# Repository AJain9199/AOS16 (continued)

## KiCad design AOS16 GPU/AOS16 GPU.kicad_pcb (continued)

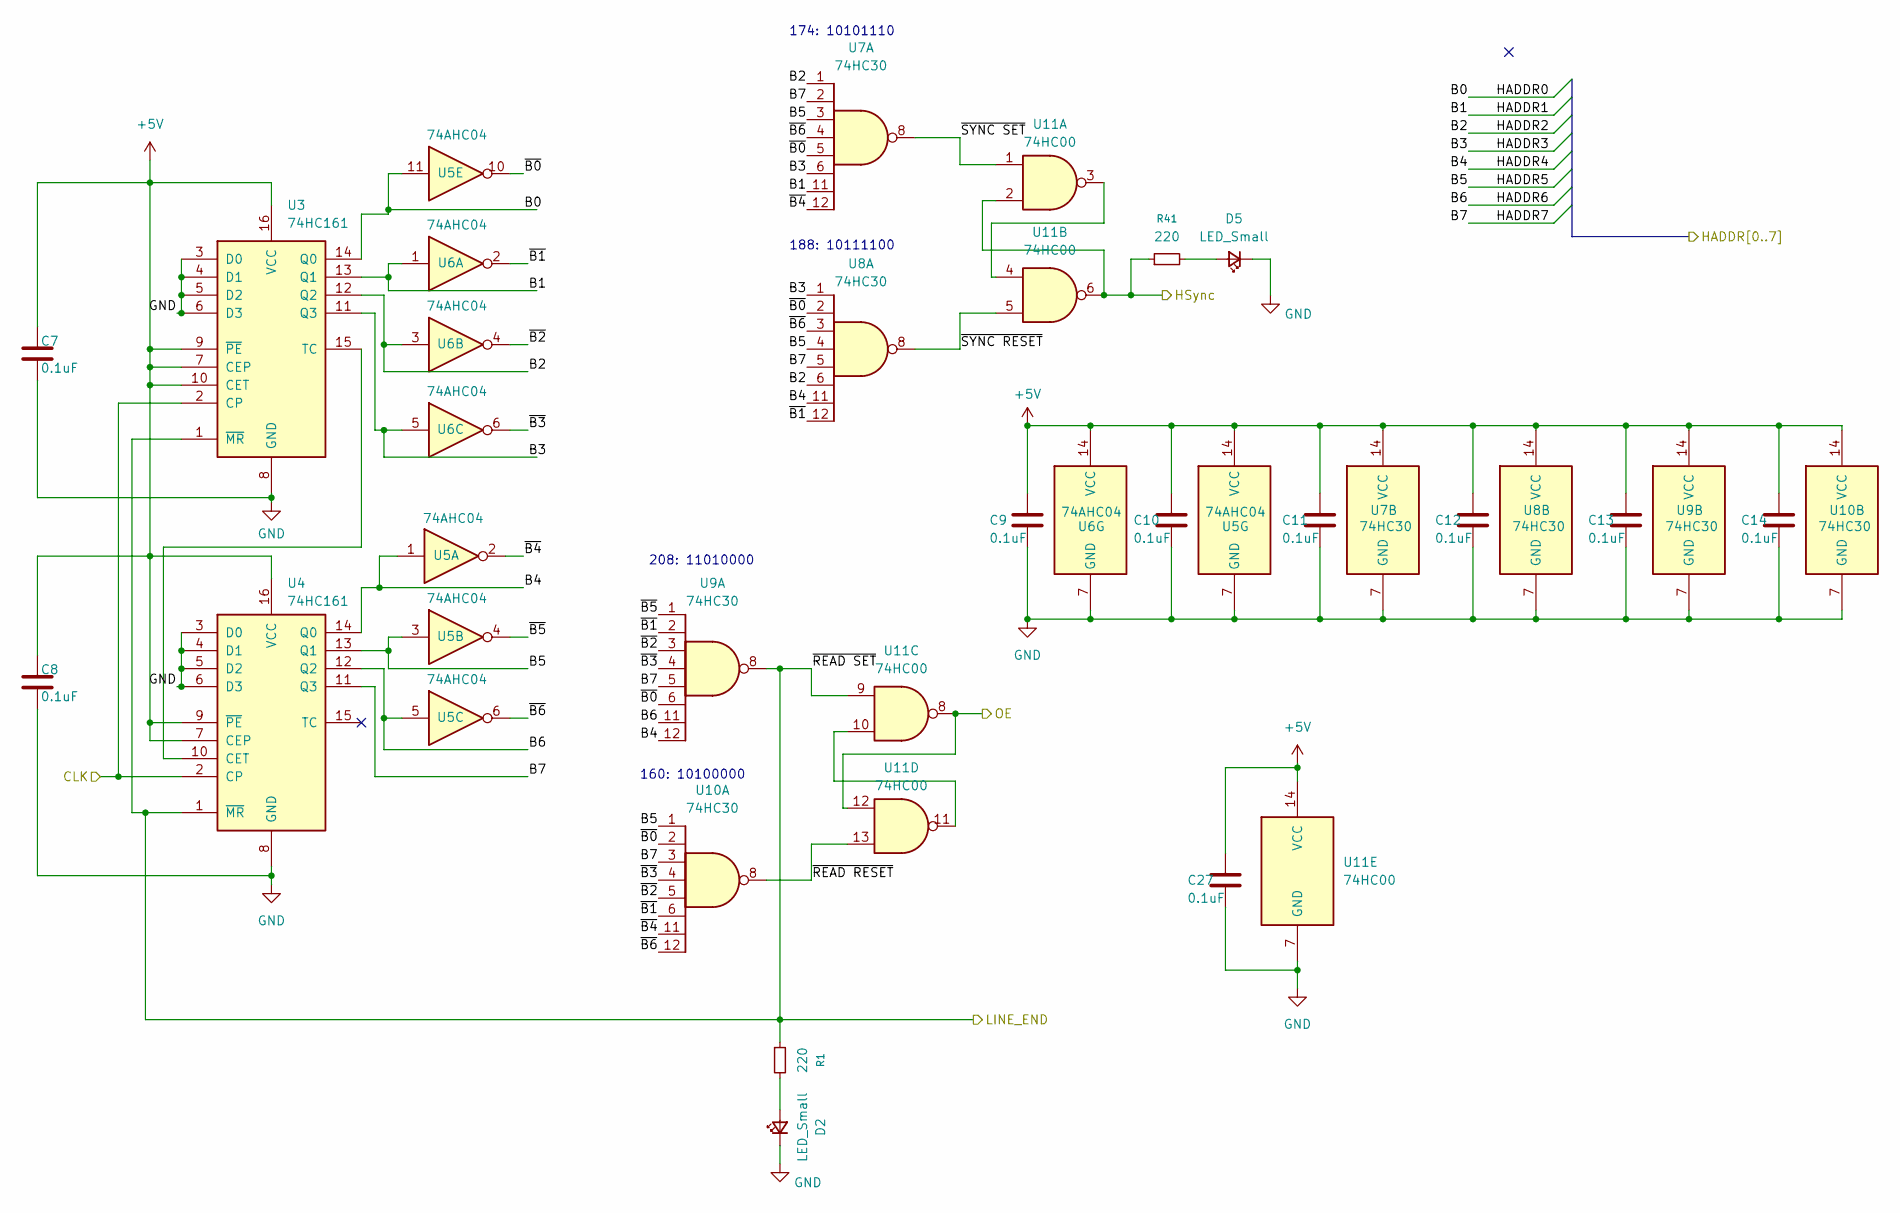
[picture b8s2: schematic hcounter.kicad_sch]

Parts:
C7, C8, C9, C10, C11, C12, C13, C14, C27: 0.1uF; C_0603_1608Metric
D2, D5: LED_Small; LED_0603_1608Metric
R1, R41: 220; R_0603_1608Metric
U3, U4: 74HC161; SOIC-16_3.9x9.9mm_P1.27mm
U5, U6: 74AHC04; SOIC-14_3.9x8.7mm_P1.27mm
U7, U8, U9, U10: 74HC30; SOIC-14_3.9x8.7mm_P1.27mm
U11: 74HC00; SOIC-14_3.9x8.7mm_P1.27mm

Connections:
+5V: C7.1, C8.1, C9.1, C10.1, C11.1, C12.1, C13.1, C14.1, C27.1, U3.7 (CEP), U3.9 (~PE), U3.10 (CET), U3.16 (VCC), U4.7 (CEP), U4.9 (~PE), U4.16 (VCC), U5.14 (VCC), U6.14 (VCC), U7.14 (VCC), U8.14 (VCC), U9.14 (VCC), U10.14 (VCC), U11.14 (VCC); also elsewhere on the board
/9mhz: U3.2 (CP), U4.2 (CP); also elsewhere on the board
/HCounter/OE: U11.8, U11.12; also elsewhere on the board
/HCounter/~B0: U5.10, U7.5, U8.2, U9.6, U10.2
/HCounter/~B1: U6.2, U8.12, U9.2, U10.6
/HCounter/~B2: U6.4, U9.3, U10.5
/HCounter/~B3: U6.6, U9.4, U10.4
/HCounter/~B4: U5.2, U7.12, U10.11
/HCounter/~B5: U5.4, U9.1
/HCounter/~B6: U5.6, U7.4, U8.3, U10.12
/HCounter/~READ RESET: U10.8, U11.13
/HCounter/~READ SET: R1.1, U3.1 (~MR), U4.1 (~MR), U9.8, U11.9; also elsewhere on the board
/HCounter/~SYNC RESET: U8.8, U11.5
/HCounter/~SYNC SET: U7.8, U11.1
/RAM_ADDR0: U3.14 (Q0), U5.11; also elsewhere on the board
/RAM_ADDR1: U3.13 (Q1), U6.1, U7.11; also elsewhere on the board
/RAM_ADDR2: U3.12 (Q2), U6.3, U7.1, U8.6; also elsewhere on the board
/RAM_ADDR3: U3.11 (Q3), U6.5, U7.6, U8.1; also elsewhere on the board
/RAM_ADDR4: U4.14 (Q0), U5.1, U8.11, U9.12; also elsewhere on the board
/RAM_ADDR5: U4.13 (Q1), U5.3, U7.3, U8.4, U10.1; also elsewhere on the board
/RAM_ADDR6: U4.12 (Q2), U5.5, U9.11; also elsewhere on the board
/RAM_ADDR7: U4.11 (Q3), U7.2, U8.5, U9.5, U10.3; also elsewhere on the board
/h_sync: R41.1, U11.2, U11.6; also elsewhere on the board
GND: C7.2, C8.2, C9.2, C10.2, C11.2, C12.2, C13.2, C14.2, C27.2, D2.1 (K), D5.1 (K), U3.3 (D0), U3.4 (D1), U3.5 (D2), U3.6 (D3), U3.8 (GND), U4.3 (D0), U4.4 (D1), U4.5 (D2), U4.6 (D3), U4.8 (GND), U5.7 (GND), U6.7 (GND), U7.7 (GND), U8.7 (GND), U9.7 (GND), U10.7 (GND), U11.7 (GND); also elsewhere on the board
unnamed: D2.2 (A), R1.2
unnamed: D5.2 (A), R41.2
unnamed: U3.15 (TC), U4.10 (CET)
unnamed: U11.3, U11.4
unnamed: U11.10, U11.11

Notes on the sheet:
160: 10100000
188: 10111100
174: 10101110
208: 11010000

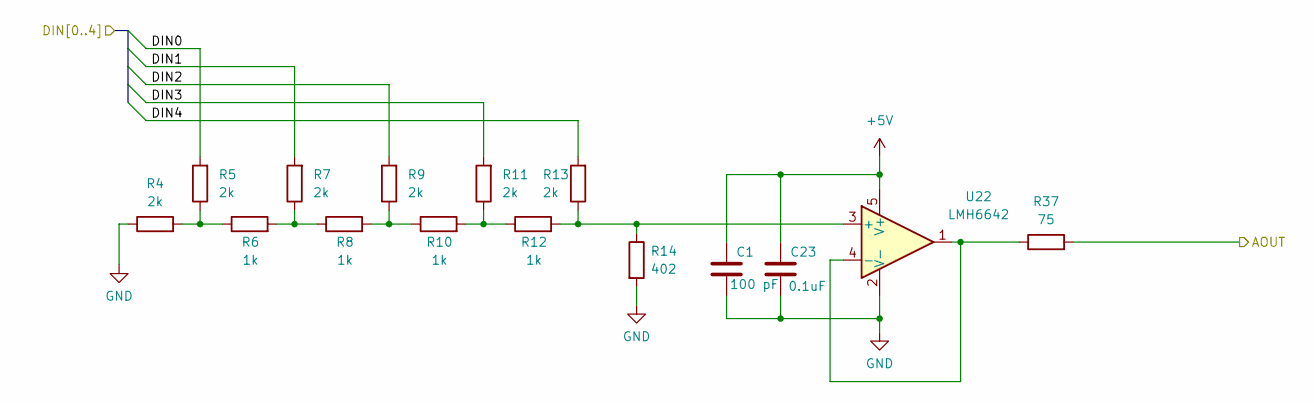
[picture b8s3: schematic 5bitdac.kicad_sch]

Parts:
C1: 100 pF; C_0603_1608Metric
C23: 0.1uF; C_0603_1608Metric
R4, R5, R7, R9, R11, R13: 2k; R_0603_1608Metric
R6, R8, R10, R12: 1k; R_0603_1608Metric
R14: 402; R_0402_1005Metric
R37: 75; R_0603_1608Metric
U22: LMH6642; SOT-23-5

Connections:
+5V: C1.1, C23.1, U22.5 (V+); also elsewhere on the board
/5-bit DAC1/AOUT: R37.2; also elsewhere on the board
/MEMIN5: R5.2; also elsewhere on the board
/MEMIN6: R7.2; also elsewhere on the board
/MEMIN7: R9.2; also elsewhere on the board
/MEMIN8: R11.2; also elsewhere on the board
/MEMIN9: R13.2; also elsewhere on the board
GND: C1.2, C23.2, R4.1, R14.2, U22.2 (V-); also elsewhere on the board
unnamed: R4.2, R5.1, R6.1
unnamed: R6.2, R7.1, R8.1
unnamed: R8.2, R9.1, R10.1
unnamed: R10.2, R11.1, R12.1
unnamed: R12.2, R13.1, R14.1, U22.3 (+)
unnamed: R37.1, U22.1, U22.4 (-)

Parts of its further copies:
C2, C4: 100 pF; C_0603_1608Metric
C24, C25: 0.1uF; C_0603_1608Metric
R15, R16, R18, R20, R22, R24, R26, R27, R29, R31, R33, R35: 2k; R_0603_1608Metric
R17, R19, R21, R23, R28, R30, R32, R34: 1k; R_0603_1608Metric
R25, R36: 402; R_0402_1005Metric
R38, R39: 75; R_0603_1608Metric
U23, U24: LMH6642; SOT-23-5

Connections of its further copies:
+5V: C2.1, C4.1, C24.1, C25.1, U23.5 (V+), U24.5 (V+); also elsewhere on the board
/5-bit DAC2/AOUT: R39.2; also elsewhere on the board
/5-bit DAC/AOUT: R38.2; also elsewhere on the board
/MEMIN0: R16.2; also elsewhere on the board
/MEMIN1: R18.2; also elsewhere on the board
/MEMIN2: R20.2; also elsewhere on the board
/MEMIN3: R22.2; also elsewhere on the board
/MEMIN4: R24.2; also elsewhere on the board
/MEMIN10: R27.2; also elsewhere on the board
/MEMIN11: R29.2; also elsewhere on the board
/MEMIN12: R31.2; also elsewhere on the board
/MEMIN13: R33.2; also elsewhere on the board
/MEMIN14: R35.2; also elsewhere on the board
GND: C2.2, C4.2, C24.2, C25.2, R15.1, R25.2, R26.1, R36.2, U23.2 (V-), U24.2 (V-); also elsewhere on the board
unnamed: R15.2, R16.1, R17.1
unnamed: R17.2, R18.1, R19.1
unnamed: R19.2, R20.1, R21.1
unnamed: R21.2, R22.1, R23.1
unnamed: R26.2, R27.1, R28.1
unnamed: R28.2, R29.1, R30.1
unnamed: R30.2, R31.1, R32.1
unnamed: R32.2, R33.1, R34.1
unnamed: R23.2, R24.1, R25.1, U23.3 (+)
unnamed: R38.1, U23.1, U23.4 (-)
unnamed: R34.2, R35.1, R36.1, U24.3 (+)
unnamed: R39.1, U24.1, U24.4 (-)

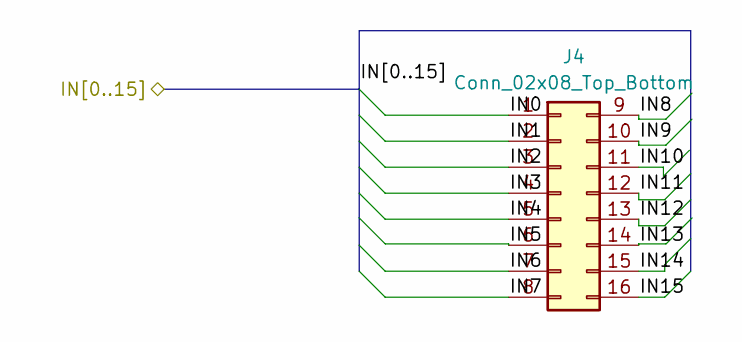
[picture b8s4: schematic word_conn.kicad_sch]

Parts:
J4: Conn_02x08_Top_Bottom; PinHeader_2x08_P2.54mm_Vertical

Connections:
/RAM_ADDR0: J4.1; also elsewhere on the board
/RAM_ADDR1: J4.2; also elsewhere on the board
/RAM_ADDR2: J4.3; also elsewhere on the board
/RAM_ADDR3: J4.4; also elsewhere on the board
/RAM_ADDR4: J4.5; also elsewhere on the board
/RAM_ADDR5: J4.6; also elsewhere on the board
/RAM_ADDR6: J4.7; also elsewhere on the board
/RAM_ADDR7: J4.8; also elsewhere on the board
/RAM_ADDR8: J4.9; also elsewhere on the board
/RAM_ADDR9: J4.10; also elsewhere on the board
/RAM_ADDR10: J4.11; also elsewhere on the board
/RAM_ADDR11: J4.12; also elsewhere on the board
/RAM_ADDR12: J4.13; also elsewhere on the board
/RAM_ADDR13: J4.14; also elsewhere on the board
/RAM_ADDR14: J4.15; also elsewhere on the board
/word_conn/IN15: J4.16

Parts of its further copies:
J5: Conn_02x08_Top_Bottom; PinHeader_2x08_P2.54mm_Vertical

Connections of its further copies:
/MEMIN0: J5.1; also elsewhere on the board
/MEMIN1: J5.2; also elsewhere on the board
/MEMIN2: J5.3; also elsewhere on the board
/MEMIN3: J5.4; also elsewhere on the board
/MEMIN4: J5.5; also elsewhere on the board
/MEMIN5: J5.6; also elsewhere on the board
/MEMIN6: J5.7; also elsewhere on the board
/MEMIN7: J5.8; also elsewhere on the board
/MEMIN8: J5.9; also elsewhere on the board
/MEMIN9: J5.10; also elsewhere on the board
/MEMIN10: J5.11; also elsewhere on the board
/MEMIN11: J5.12; also elsewhere on the board
/MEMIN12: J5.13; also elsewhere on the board
/MEMIN13: J5.14; also elsewhere on the board
/MEMIN14: J5.15; also elsewhere on the board
/MEMIN15: J5.16

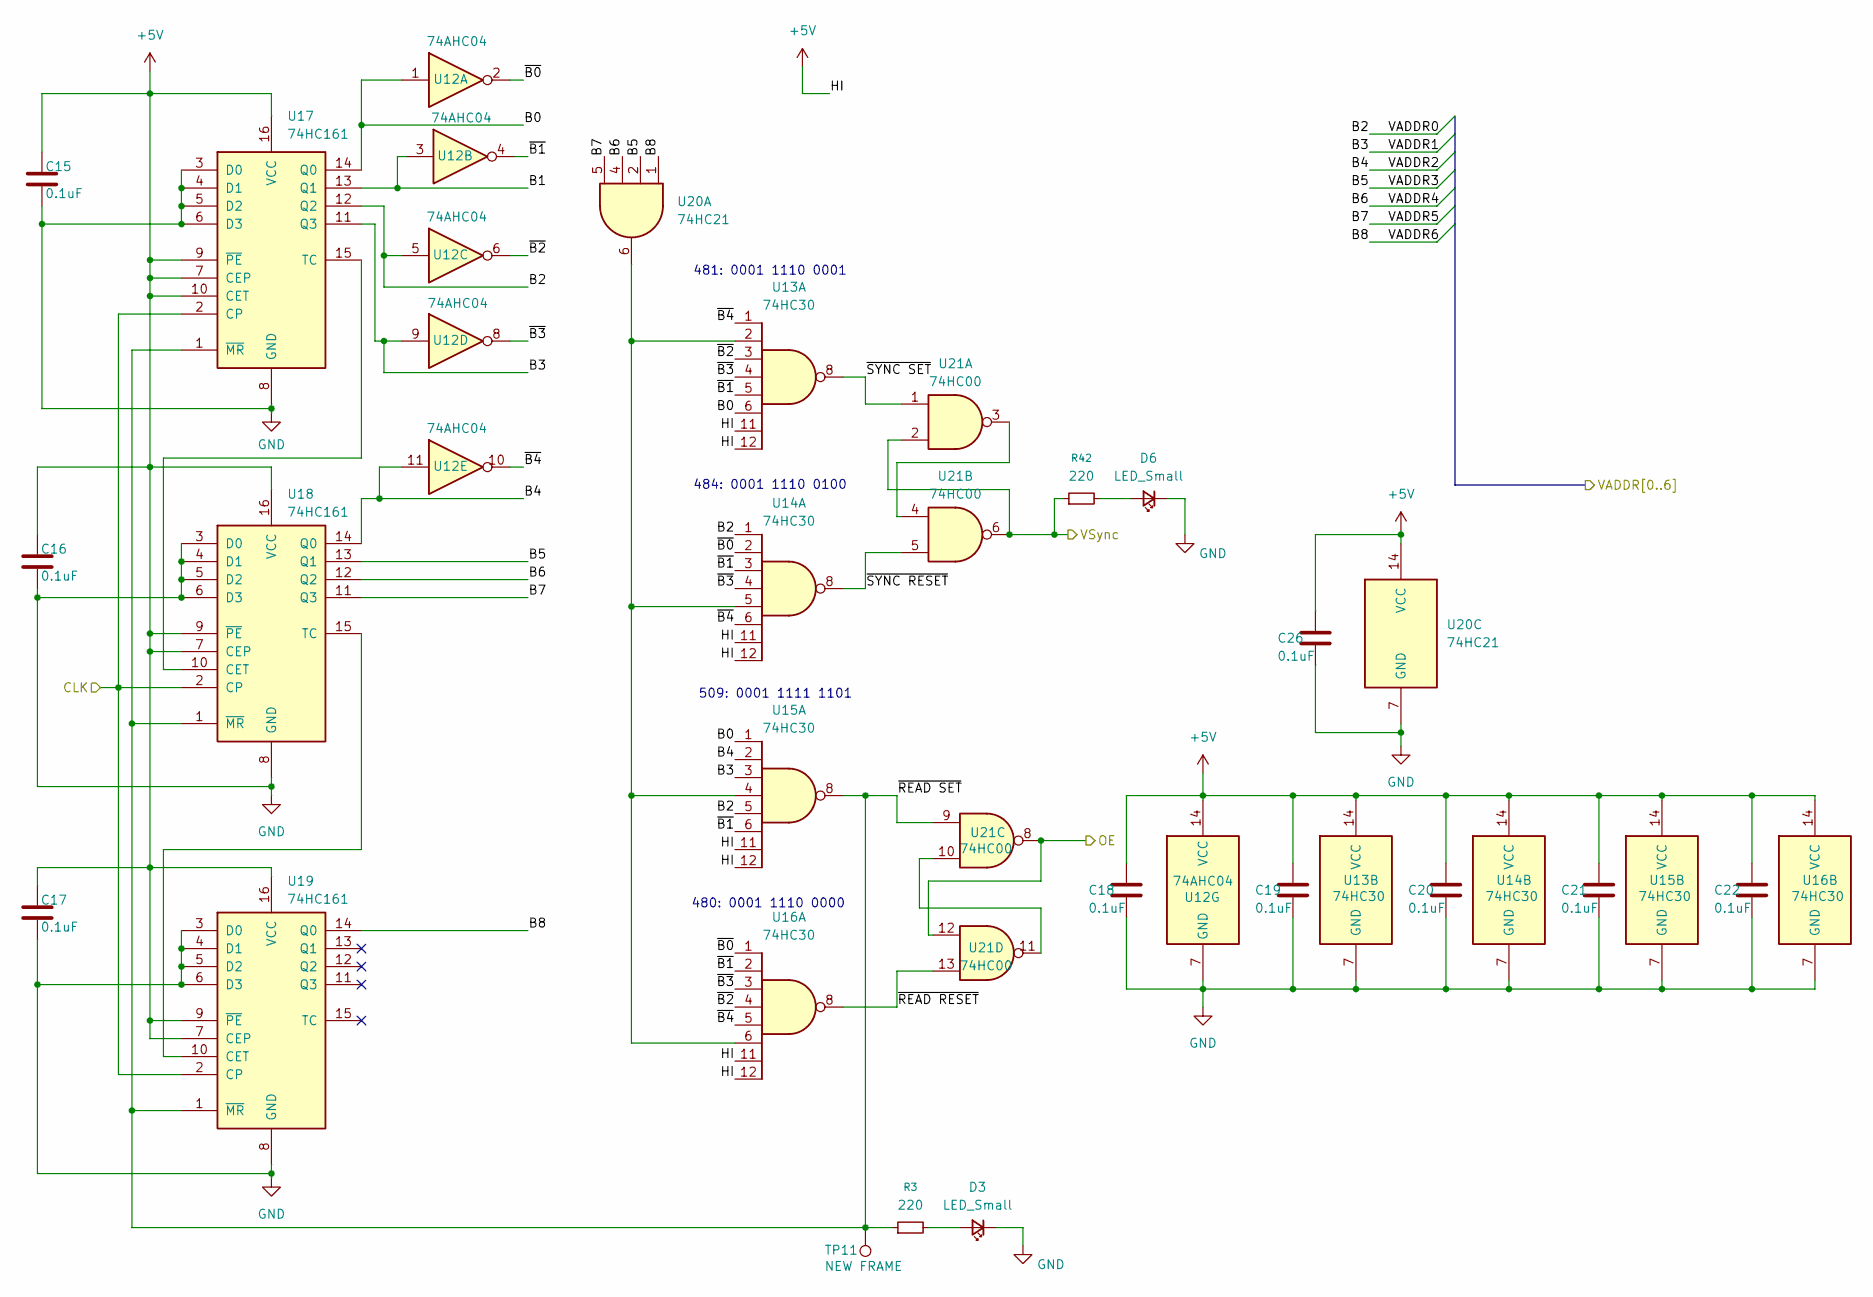
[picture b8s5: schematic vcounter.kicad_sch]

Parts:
C15, C16, C17, C18, C19, C20, C21, C22, C26: 0.1uF; C_0603_1608Metric
D3, D6: LED_Small; LED_0603_1608Metric
R3, R42: 220; R_0603_1608Metric
TP11: NEW FRAME; TestPoint_Pad_D2.0mm
U12: 74AHC04; SOIC-14_3.9x8.7mm_P1.27mm
U13, U14, U15, U16: 74HC30; SOIC-14_3.9x8.7mm_P1.27mm
U17, U18, U19: 74HC161; SOIC-16_3.9x9.9mm_P1.27mm
U20: 74HC21; SOIC-14_3.9x8.7mm_P1.27mm
U21: 74HC00; SOIC-14_3.9x8.7mm_P1.27mm

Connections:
+5V: C15.1, C16.1, C17.1, C18.1, C19.1, C20.1, C21.1, C22.1, C26.1, U12.14 (VCC), U13.11, U13.12, U13.14 (VCC), U14.11, U14.12, U14.14 (VCC), U15.11, U15.12, U15.14 (VCC), U16.11, U16.12, U16.14 (VCC), U17.7 (CEP), U17.9 (~PE), U17.10 (CET), U17.16 (VCC), U18.7 (CEP), U18.9 (~PE), U18.16 (VCC), U19.7 (CEP), U19.9 (~PE), U19.16 (VCC), U20.14 (VCC); also elsewhere on the board
/HCounter/~READ SET: U17.2 (CP), U18.2 (CP), U19.2 (CP); also elsewhere on the board
/RAM_ADDR8: U12.5, U14.1, U15.5, U17.12 (Q2); also elsewhere on the board
/RAM_ADDR9: U12.9, U15.3, U17.11 (Q3); also elsewhere on the board
/RAM_ADDR10: U12.11, U15.2, U18.14 (Q0); also elsewhere on the board
/RAM_ADDR11: U18.13 (Q1), U20.2; also elsewhere on the board
/RAM_ADDR12: U18.12 (Q2), U20.4; also elsewhere on the board
/RAM_ADDR13: U18.11 (Q3), U20.5; also elsewhere on the board
/RAM_ADDR14: U19.14 (Q0), U20.1; also elsewhere on the board
/VCounter/B0: U12.1, U13.6, U15.1, U17.14 (Q0)
/VCounter/B1: U12.3, U17.13 (Q1)
/VCounter/OE: U21.8, U21.12; also elsewhere on the board
/VCounter/~B0: U12.2, U14.2, U16.1
/VCounter/~B1: U12.4, U13.5, U14.3, U15.6, U16.2
/VCounter/~B2: U12.6, U13.3, U16.4
/VCounter/~B3: U12.8, U13.4, U14.4, U16.3
/VCounter/~B4: U12.10, U13.1, U14.6, U16.5
/VCounter/~READ RESET: U16.8, U21.13
/VCounter/~READ SET: R3.1, TP11.1, U15.8, U17.1 (~MR), U18.1 (~MR), U19.1 (~MR), U21.9
/VCounter/~SYNC RESET: U14.8, U21.5
/VCounter/~SYNC SET: U13.8, U21.1
/v_sync: R42.1, U21.2, U21.6; also elsewhere on the board
GND: C15.2, C16.2, C17.2, C18.2, C19.2, C20.2, C21.2, C22.2, C26.2, D3.1 (K), D6.1 (K), U12.7 (GND), U13.7 (GND), U14.7 (GND), U15.7 (GND), U16.7 (GND), U17.3 (D0), U17.4 (D1), U17.5 (D2), U17.6 (D3), U17.8 (GND), U18.3 (D0), U18.4 (D1), U18.5 (D2), U18.6 (D3), U18.8 (GND), U19.3 (D0), U19.4 (D1), U19.5 (D2), U19.6 (D3), U19.8 (GND), U20.7 (GND); also elsewhere on the board
unnamed: D3.2 (A), R3.2
unnamed: D6.2 (A), R42.2
unnamed: U13.2, U14.5, U15.4, U16.6, U20.6
unnamed: U17.15 (TC), U18.10 (CET)
unnamed: U18.15 (TC), U19.10 (CET)
unnamed: U21.3, U21.4
unnamed: U21.10, U21.11

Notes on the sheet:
480: 0001 1110 0000
484: 0001 1110 0100
509: 0001 1111 1101
481: 0001 1110 0001

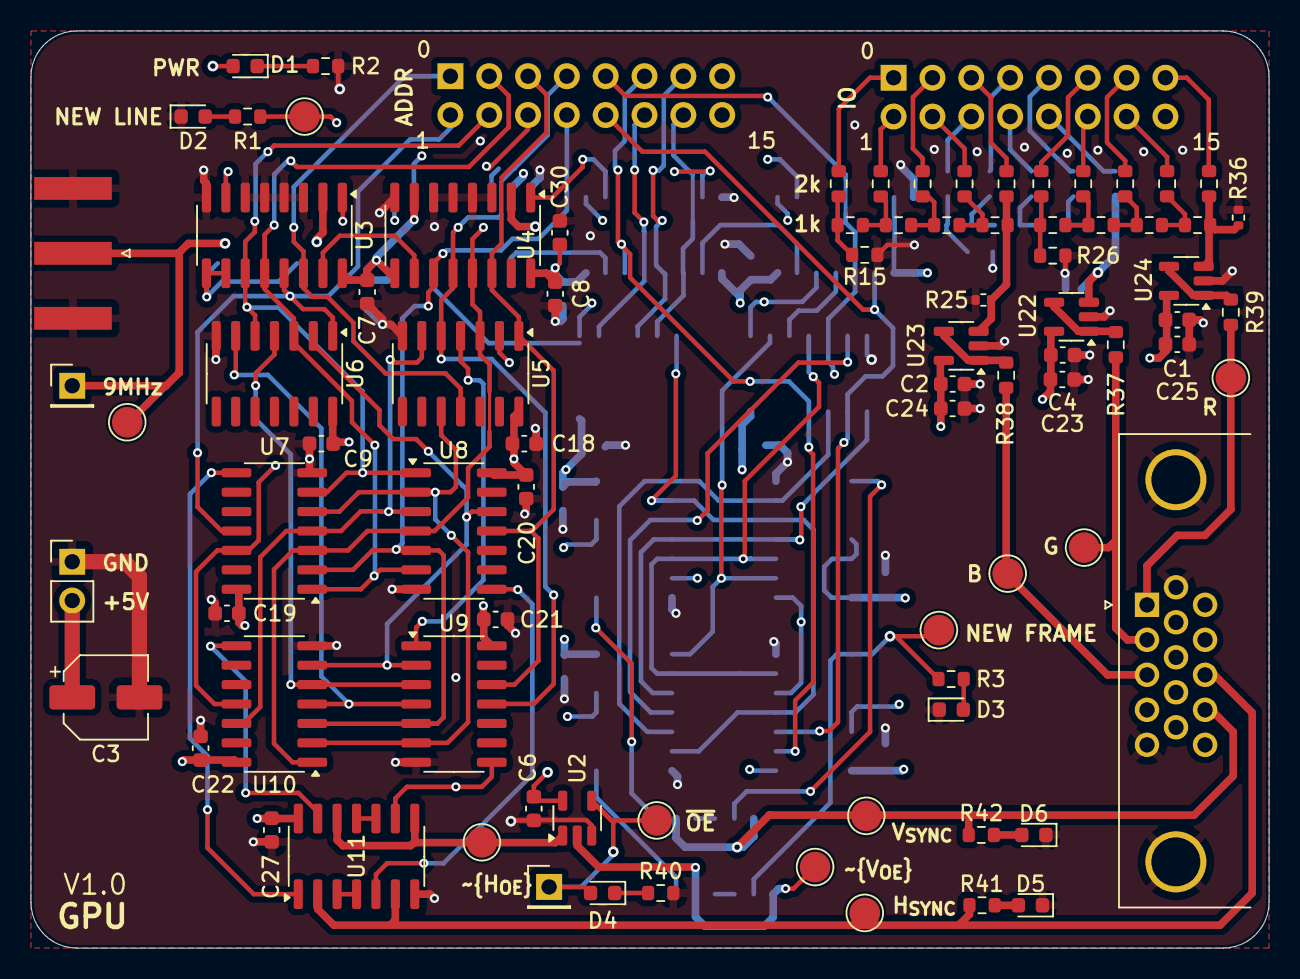
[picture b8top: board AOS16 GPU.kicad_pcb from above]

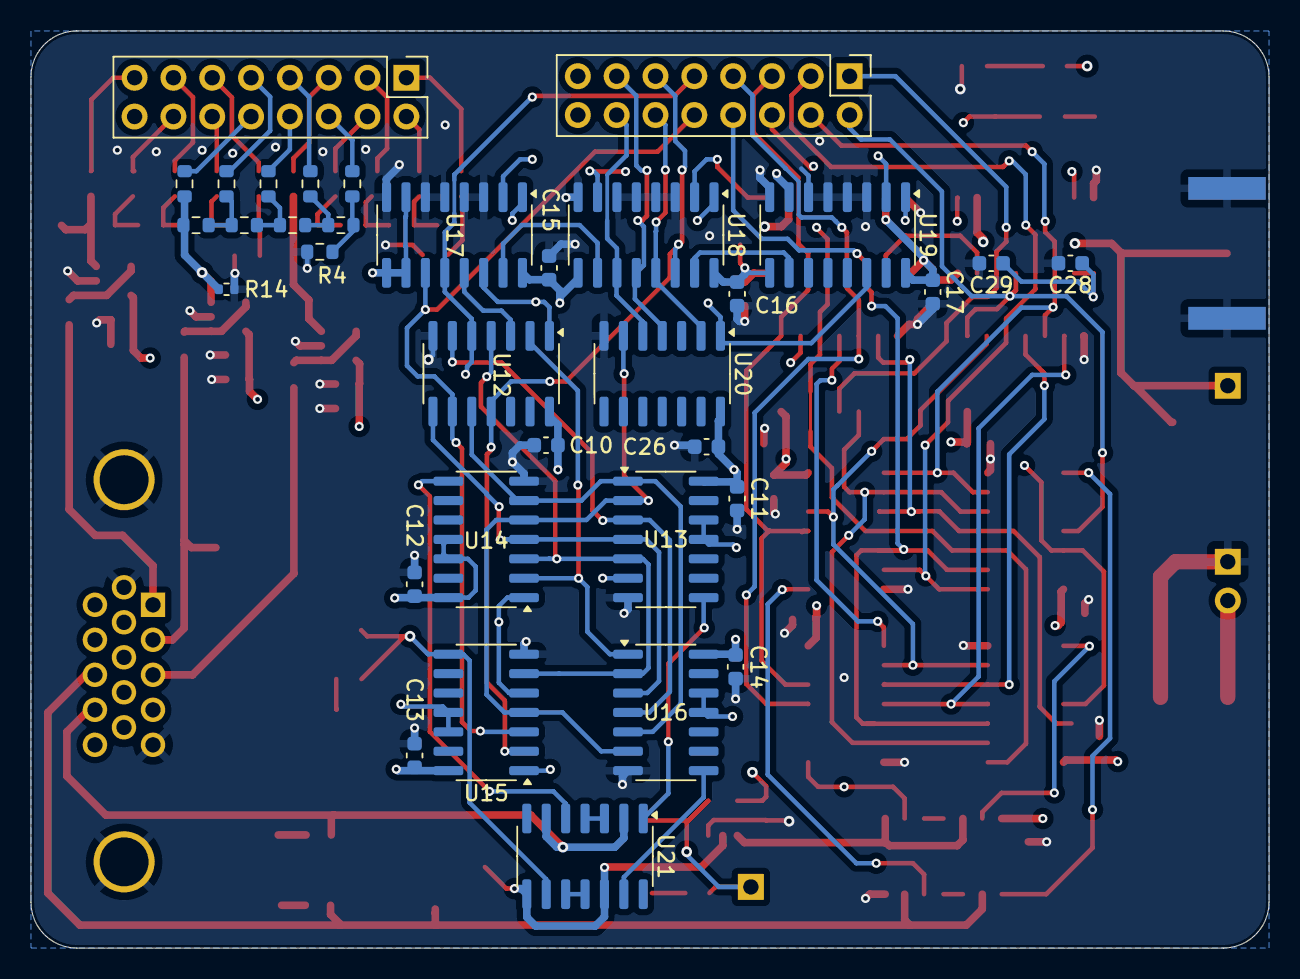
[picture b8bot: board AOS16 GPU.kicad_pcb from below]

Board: 4 copper layers, 81.0 x 60.0 mm, 118 parts (34 on the bottom side), 95 nets.

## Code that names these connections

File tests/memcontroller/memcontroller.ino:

#include "Arduino.h"

#define SETMODE(MODE) for (int i = 2; i < 18; i++) {pinMode(i, MODE);}

void writeData(uint16_t data) {
  SETMODE(OUTPUT);
  for (int i = 2; i < 18; i++) {
    digitalWrite(i, (data >> (i-2)) & 1);
  }
}

uint16_t readData() {
  SETMODE(INPUT);
  uint16_t data = 0;
  for (int i = 2; i < 18; i++) {
    data |= ((uint16_t)digitalRead(i) << (i-2));

  }
  return data;
}

uint16_t mangler(uint16_t input) {
  uint64_t tmp = (uint64_t) input;
  return (uint16_t) ((tmp * 0x9E37 ^ (tmp >> 3)) & 0xffff);
}

#define MAL 19
#define RSE 21
#define CRE 23
#define CWE 25
#define DBS 27
#define CLK 29

void loadAddr(uint16_t addr) {
  digitalWrite(CLK, 0);
  writeData(addr);
  digitalWrite(MAL, 1);

  digitalWrite(CLK, 1);


  digitalWrite(CLK, 0);
  digitalWrite(MAL, 1);
}

void readCheck() {
  digitalWrite(CRE, 1);
  
  for (uint16_t i = 0; i < 0x7fff; i++) {
    loadAddr(i);
    if (i % 1000 == 0) {
      Serial.print(".");
    }

    SETMODE(INPUT);
    digitalWrite(CRE, 0);

    uint16_t data = readData();

    if (data != mangler(i)) {

    Serial.print("At address ");
    Serial.print(i);
    Serial.print(" | Expected ");
    Serial.print(mangler(i));
    Serial.print(" got ");
    Serial.print(data);
     Serial.print(" xor ");  Serial.println(data ^
  mangler(i), HEX);
    }
    digitalWrite(CRE, 1);
  }

  Serial.println("\nTests complete."); 
}

void checkROM() {
  Serial.print("Begun ROM test (using hash)...");
  digitalWrite(RSE, 1);
  readCheck();
}

void checkRAM() {
  Serial.print("Begun RAM test (using hash)...\n");
  digitalWrite(RSE, 0);

  Serial.print("Writing...");
  for (uint16_t i = 0; i < 0x7fff; i++) {
    loadAddr(i);
    writeData(mangler(i));
    
    if (i % 1000 == 0) {
      Serial.print(".");
    }

    digitalWrite(CWE, 0);
    delayMicroseconds(1);
    digitalWrite(CWE, 1);
  }
  
  Serial.print("\nReading...");

  readCheck();
}

void setup() {
  Serial.begin(115200);
  pinMode(MAL, OUTPUT);
  pinMode(CLK, OUTPUT);

  pinMode(CRE, OUTPUT);
  pinMode(CWE, OUTPUT);
  pinMode(RSE, OUTPUT);
  pinMode(DBS, OUTPUT);

  digitalWrite(CRE, 1);
  digitalWrite(CWE, 1);
  digitalWrite(RSE, 1);
  checkRAM();
}

void loop() {}

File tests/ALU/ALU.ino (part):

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// ---- Pin Definitions (unchanged from original) --------------
#define CLK  A6
#define nOE  A2
#define Cout A3   // Carry-out from MSB chip (input to Arduino)
#define S2   51
#define S1   49
#define S0   52
#define S3   53
#define M    48
#define nCin 50   // Active-LOW carry-in
#define INB  A4
#define INA  A5

// ---- Test Bookkeeping ---------------------------------------
static int gPassed = 0;
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  // ---- Pin modes (unchanged from original) ------------------
  pinMode(CLK,  OUTPUT);
  pinMode(nOE,  OUTPUT);
  pinMode(Cout, INPUT);
  pinMode(S0,   OUTPUT);
  pinMode(S1,   OUTPUT);
  pinMode(S2,   OUTPUT);
  pinMode(S3,   OUTPUT);
  pinMode(M,    OUTPUT);
  pinMode(nCin, OUTPUT);
  pinMode(INA,  OUTPUT);
  pinMode(INB,  OUTPUT);
  pinMode(A0,   OUTPUT);
  pinMode(A1,   OUTPUT);

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
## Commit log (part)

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2025-02-15 Completed ROM ID check
2025-02-15 Setup comms between arduino and host
2025-02-16 Completed ROM write functionality
2025-02-19 Working read and write
2025-02-20 Increased flash programmer performance
2025-02-20 cleaned up KiCad temporary files
2025-02-21 reduced buffer size to comply with arduino serial buffer
2025-02-21 Removed address-based reading and writing
2025-02-21 Completed flash I/O
2025-02-21 updated double buffer
2025-02-22 added flash readme
2025-02-26 Added Logisim schematic
2025-03-02 Completed double buffer first draft
2025-03-02 Finalized double buffer
2025-03-04 Added base Logisim schematic and microcode
2025-03-05 Added ALU function mapping and reg to reg mov instruction
2025-03-06 Added stack instructions
2025-03-07 Began working on assembler
2025-03-07 added eat methods
2025-03-07 created basic assembly parser
2025-03-07 added helper methods
2025-03-08 completed basic translation
2025-03-08 Added machine code output and misc fixes
2025-03-08 completed assembler framework
2025-03-09 fixed uint8 and uint16 directives
2025-03-22 Double Buffer Revision
2025-03-22 Completed ALU first draft
2025-03-22 microcode refactoring
2025-03-31 Updated ALU and moved common schematics to common/ for enhanced reusability
2025-03-31 Fixed double buffer logic families
2025-04-02 Fixed tri-state buffer and completed double buffer PCB
2025-04-02 Fixed ERC errors
2025-04-03 Made tri-state and register schematic look nice
2025-04-03 Fixed ALU silkscreen for new fab
2025-04-03 Fixed silkscreen on ALU and Double Buffer
2025-05-27 Started GPU
2025-05-27 Added horizontal counting circuit
2025-06-01 Completed GPU schematic
2025-06-05 Migrated to KiCad 9.0 and made changes to GPU
2025-06-16 Fixed incorrect wiring in ALU (input registers)
2025-06-22 Fixed ALU error
2025-06-22 Changed register in logisim circuit
2025-06-23 Fixed logisim error
2025-06-23 Added ALU flags
2025-06-23 Assembler fix- removed extra zeros
2025-06-23 Fixed wiring error
2025-06-23 Added no-operand instructions
2025-06-23 fixed microcode
2025-06-23 Completed reg4x16
2025-07-06 Added negative constants to assembler
2025-07-21 Added Jump-if-not-zero instruction: Turing complete now
2025-09-03 Fixed register data flow direction and added mounitng holes to ALU
2025-09-04 Added arduino test for 74HC670
2025-09-04 Refactored files, finalized reg4x16, and used lowercase v
2025-09-08 Memory Controller- Initial setup
2025-09-13 Memory Controller first draft
2025-10-10 Software update: firmware update, assembler fixes and sim fixes for a fibonacci sequence program
2025-10-16 Ported simulation to Digital with working VGA screen
2025-10-17 Fixed JNZ
2025-10-22 Control Unit first draft
2025-10-23 Refactored instructions and ALU mapping
2025-10-23 Added CMP and NEG instructions
2025-10-23 Completed instruction refactor
2025-10-24 fixed push/pop instructions
2025-10-24 Added call instruction
2025-10-24 Added ret instruction
2025-11-09 Memory Controller fabrication checks complete
2025-12-17 Cleanup, added photos and README overhaul
2025-12-17 actually overhauled the readme
2025-12-17 README edits
2026-01-18 Finalized Control unit for fabrication
2026-01-18 Updated README tracker
2026-03-11 Added tests for ALU (ALL PASSING)
2026-03-11 Added tests for reg4x6 (ALL PASSING)
2026-03-11 Updated progress tracker (completed mem controller fabrication)
2026-03-11 Updated control unit and finalized for fabrication
2026-03-24 Added ROM programmer firmware
2026-03-29 Added clock circuit schematic
2026-04-11 Finalized clock for fabrication
2026-04-12 cleanup
2026-04-12 Overhauled program counter schematic
2026-05-28 GPU PCB Design v1
2026-05-31 Added bus connector
2026-06-05 Updated sim schematic GPU to match new arch
2026-06-06 Added ROM programmer interface code + changed pinout
2026-06-13 updated gpu
2026-06-13 added bus boards, bus probe, bus terminator and distribution board
2026-06-13 Added program counter PCB
2026-06-13 updated progress tracker!
2026-06-14 Updated silkscreen and cascade wiring program counter
2026-06-29 Added ROM-pointer operations
2026-06-29 fixed simulation gpu
2026-06-29 fixed ALU operand order which caused wrong subtraction ops
2026-06-29 basic character bitmap implementation
2026-06-29 implemented compressed char bitmap, added custom bitmap font
2026-06-29 Added call/ret commands
2026-06-29 assembler bug fixes
2026-06-29 working hello world example (actual text on screen)
2026-06-29 added macros to assembler
